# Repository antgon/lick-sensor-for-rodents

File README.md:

# Lick sensor for rodents

A device for measuring licking behaviour in rodents in real time.

This project describes a lick sensor developed for the purpose of
measuring licking behaviour in laboratory animals. Licking behaviour,
and in particular the analysis of lick microstructure, is a useful tool
for studying ingestive behaviour, motivation, and food preference.

2021-2025 Antonio González

## Features

The lick sensor is built with a Raspberry Pi Pico microcontroller board
and a capacitive touch sensor. It can can be used with standard water
bottles for rodents, and does not require modifications to animal home
cages. The lick sensor can thus be adapted to a wide range of
experimental setups.

Licks are detected in real time with millisecond precision from one or
many drink bottles simultaneously. The data can be recorded using any
standard data acquisition system; it can be sent to a computer for
storage; and/or it can be used for real-time control of additional
laboratory hardware such as LEDs for optogenetics.

### Variants

Different variants of the lick sensor are possible, depending on the
number of drink bottles required, and also on whether lick data is to be
recorded "raw" (i.e. as a continuous vector of on/off, digital data
samples), or saved in the form of lick events (timestamps).

Details of each of these options can be found in the relevant
directories. Briefly,

* [**One bottle, one BNC output**](bottle-x1-bnc-out). This is the
  simplest lick sensor variant: it uses only one drink bottle. Licks
  from this bottle are detected and directed to a BNC connector from
  where they can be recorded with a data acquisition system and/or used
  for driving additional laboratory hardware in real time.

* [**Several bottles, BNC outputs**](bottle-x6-bnc-out). Similar to the
  setup above but using more than one drink bottle.

* [**Many bottles (up to 12), USB output**](bottle-x12-usb-out). Here,
  lick events (timestamps) from many drink bottles are detected and sent
  to a computer connected to the microcontroller with a USB cable. The
  construction of this lick sensor is very simple and a data-acquisition
  system is not required. On the other hand, the software side of it is
  more elaborate: it is necessary to install and run Python software in
  the host computer.

* [**Many bottles (up to 24), USB output**](bottle-x24-usb-out). As
  above, but using 2 touch-detection boards to handle up to 24 drink
  bottles simultaneously.

## Requirements

### Lick sensor hardware

* Drinking bottle(s). Any standard drinking bottle for rodents should
  work. We use the Crystal Deluxe Mini Bottle 75 ml ([Classic Pet
  Products, UK, cat. num.
  0190](https://classicpetproducts.co.uk/product/crystal-deluxe-mini-bottle-75ml/))
  obtained from a local pet shop.
* [Raspberry Pi
  Pico](https://www.raspberrypi.com/products/raspberry-pi-pico)
  microcontroller board.
* Capacitive touch sensor module. We use [Adafruit product ID
  1982](https://www.adafruit.com/product/1982); up to 12 water bottles
  can be connected to one of these modules[^1]. Other manufacturers sell
  touch sensors based on the MPR121 and any of these should work equally
  well.
* Stranded-core cable (e.g. 24 AWG or 26 AWG standard hook-up cable).
* A USB cable for the Raspberry Pi Pico.
* BNC connector(s). Optional, depending on the sensor variant chosen.

Some means to put the components together, for example:

* Perforated board or stripboard.
* Jumper wires.
* Soldering tools.

Supplier information and ordering codes are listed in
[material.md](docs/material.md).

### Lick sensor software

* C development tools and the knowledge/ability to build a project for
  the Raspberry Pi Pico, as described in the [Pico
  documentation](https://datasheets.raspberrypi.com/pico/getting-started-with-pico.pdf).
* MPR121 library for the Raspberry Pi Pico, available at
  https://github.com/antgon/pico-mpr121.

### Data acquisition hardware

Depending on the variant chosen, you will need either:

* A standard laboratory data-acquisition system. This is only needed
  if you want to record *raw* data (e.g.
  [bottle-x1-bnc-out](bottle-x1-bnc-out)), or
* A computer to record lick events. We use a Raspberry Pi 4 computer
  with very good results. See [bottles-x12-usb-out](bottles-x12-usb-out)
  for details.

[^1]: Adafruit sell two different MPR121 touch sensor breakouts under
    the same Product ID 1982: the original, header-only version, and the
    STEMMA QT version. Both work in the same way, and the PCBs are the
    same size (and look similar). Be aware, however, that **the pins are
    in a different order**.

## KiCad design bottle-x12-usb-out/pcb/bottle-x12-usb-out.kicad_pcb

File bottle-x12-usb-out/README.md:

# Lick sensor: up to 12 bottles, detect lick events

This variant of the sensor detects licks from up to 12 drink bottles
simultaneously. Lick events (timestamps) are sent to a host computer
connected to the Raspberry Pi Pico via a USB cable.

## Wiring and operation

Wiring of the components is simple and a stripboard can be used to
facilitate this; see folder [pcb](pcb).

For logging the data, a host computer connected to the lick sensor must
read and save the data received. We use for that a Raspberry Pi 4 (or 5)
computer:

* Compile `lick_events_usb.c` and flash into the Pico.
* Save the provided Python script (`lick_events_reader.py`) to the host
  computer.
* Connect the drink bottles to the lick sensor.
* Connect the Pico to the host computer.
* Boot the host computer. Open a terminal and run the Python script
  above. Lick data will be logged to a local text file. To stop, press
  Ctrl+C.
* To convert the data in the text file to a more readable form suitable
  for analysis, run the Python script
  [`events-to-long.py`](../utils/events-to-long.py).

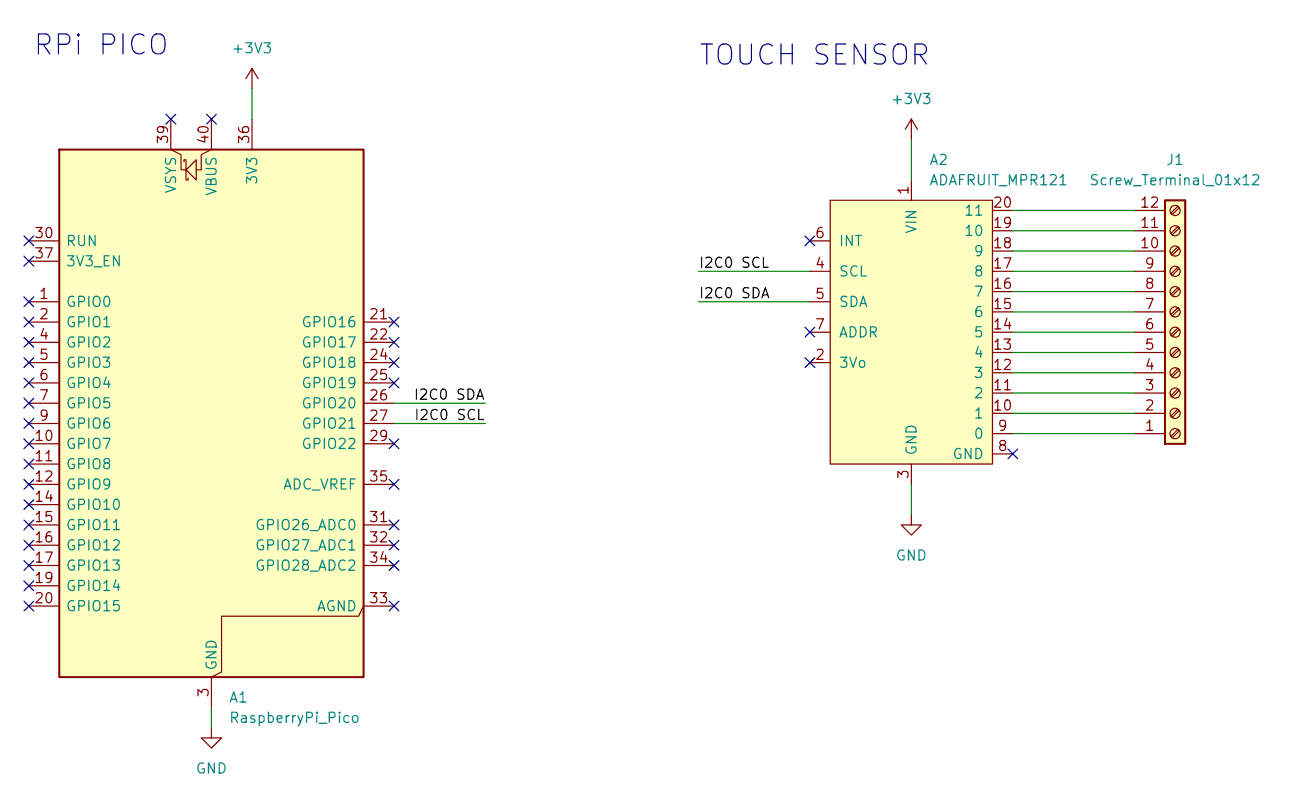
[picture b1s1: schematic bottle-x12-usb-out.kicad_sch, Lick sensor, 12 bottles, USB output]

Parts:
A1: RaspberryPi_Pico; RaspberryPi_Pico_Common_THT
A2: ADAFRUIT_MPR121
J1: Screw_Terminal_01x12; TerminalBlock_Phoenix_MPT-0,5-12-2.54_1x12_P2.54mm_Horizont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

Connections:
+3V3: A1.36 (3V3), A2.1 (VIN)
/I2C0 SCL: A1.27 (GPIO21), A2.4 (SCL)
/I2C0 SDA: A1.26 (GPIO20), A2.5 (SDA)
GND: A1.3 (GND), A1.8 (GND), A1.13 (GND), A1.18 (GND), A1.23 (GND), A1.28 (GND), A1.38 (GND), A2.3 (GND)
unnamed: A2.9 (0), J1.1
unnamed: A2.10 (1), J1.2
unnamed: A2.11 (2), J1.3
unnamed: A2.12 (3), J1.4
unnamed: A2.13 (4), J1.5
unnamed: A2.14 (5), J1.6
unnamed: A2.15 (6), J1.7
unnamed: A2.16 (7), J1.8
unnamed: A2.17 (8), J1.9
unnamed: A2.18 (9), J1.10
unnamed: A2.19 (10), J1.11
unnamed: A2.20 (11), J1.12

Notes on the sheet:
TOUCH SENSOR
RPi PICO

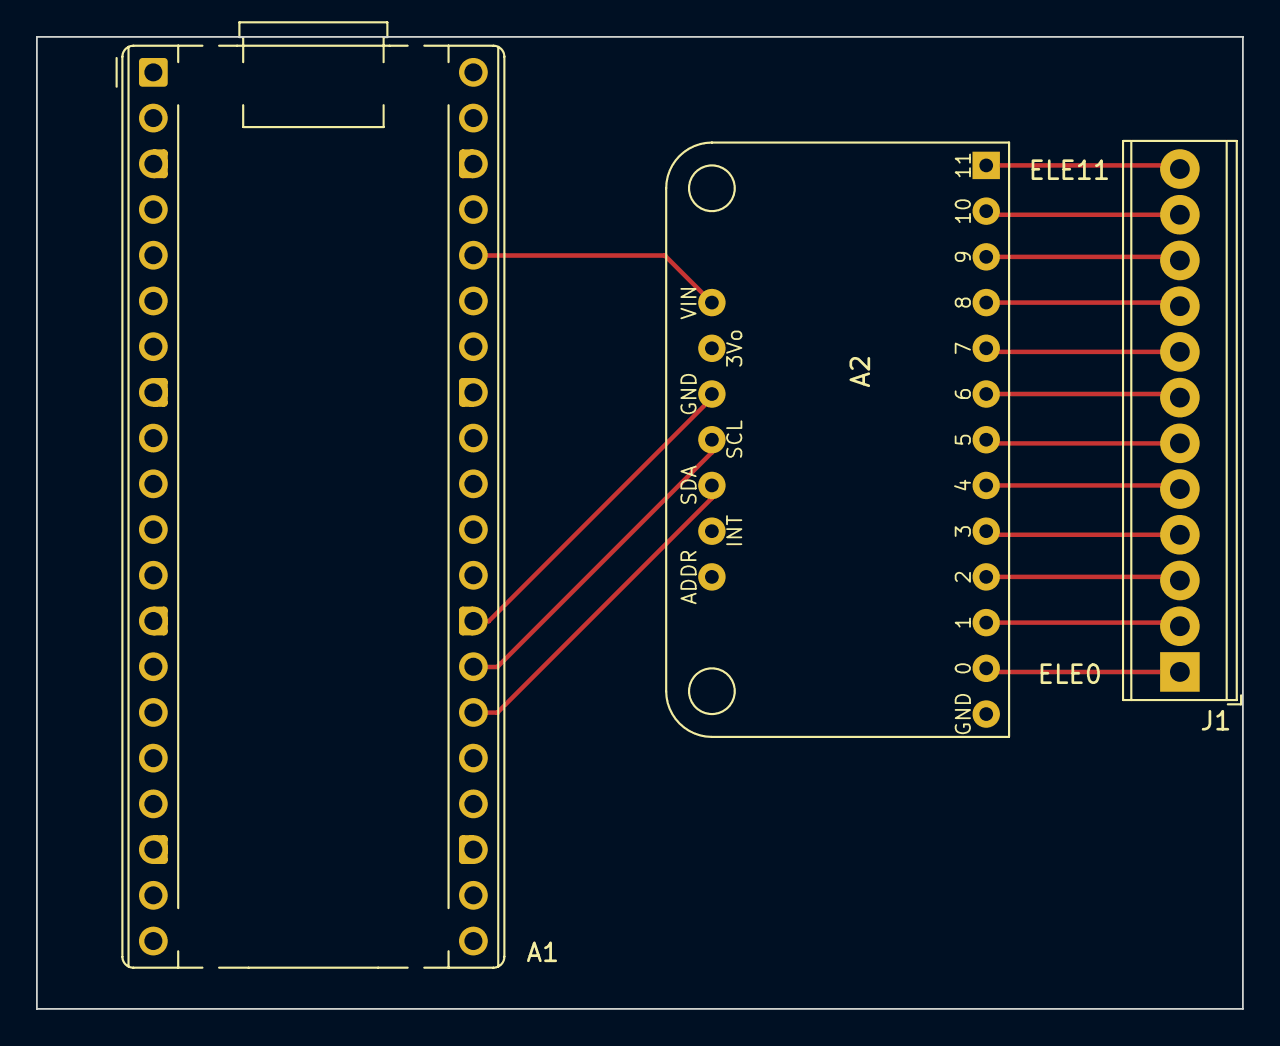
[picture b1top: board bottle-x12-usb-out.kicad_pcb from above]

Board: 2 copper layers, 67.0 x 54.0 mm, 3 parts (0 on the bottom side), 16 nets.

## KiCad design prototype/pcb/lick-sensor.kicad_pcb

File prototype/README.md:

# Lick sensor prototype

This prototype was designed for testing the lick sensor while observing
the effects of changing the sensor's settings: an LCD and four push
buttons allow to change the settings of the MPR121 capacitive sensor on
the fly. This helps tune the sensor and evaluate its ability to detect
licks under varying circumstances.

There are two BNC connectors: one outputs the digital signal, i.e. 0s
and 1s, with 1s indicating licks. The other outputs the analog signal
from the capacitive sensor, which helps visualise the changes in
capacitance that occur with licking. With these two outputs connected to
a data acquisition board, the behaviour of the touch sensor can be
assessed.

## Building and operation

1. This prototype is designed to be built on a perforated board. Details
   can be found in the [pcb](pcb) folder.

2. Program the microcontroller: compile `app/main.c` and flash into the
   Raspberry Pi Pico. See the [Pico
   documentation](https://www.raspberrypi.com/documentation/microcontrollers/pico-series.html#documentation)
   for details of how to do this. Note that in addition to standard Pico
   libraries, these 3 libraries are required:
    * [lcd16x2_i2c.h](https://github.com/antgon/pico-lcd16x2_i2c)
    * [mcp48x1.h](https://github.com/antgon/pico-mcp48x1)
    * [mpr121.h](https://github.com/antgon/pico-mpr121)

3. Connect a drink bottle to the board. Connect the two BNC outputs to a
   data acquisition (DAQ) board. Power up the Raspberry Pi Pico. The
   lick sensor will output data to the BNCs every 20 ms (50 Hz).

4. Modify the MCP121 settings using the buttons (see [docs](docs)
   for detailed instructions), use the DAQ to observe the effects of
   doing this.

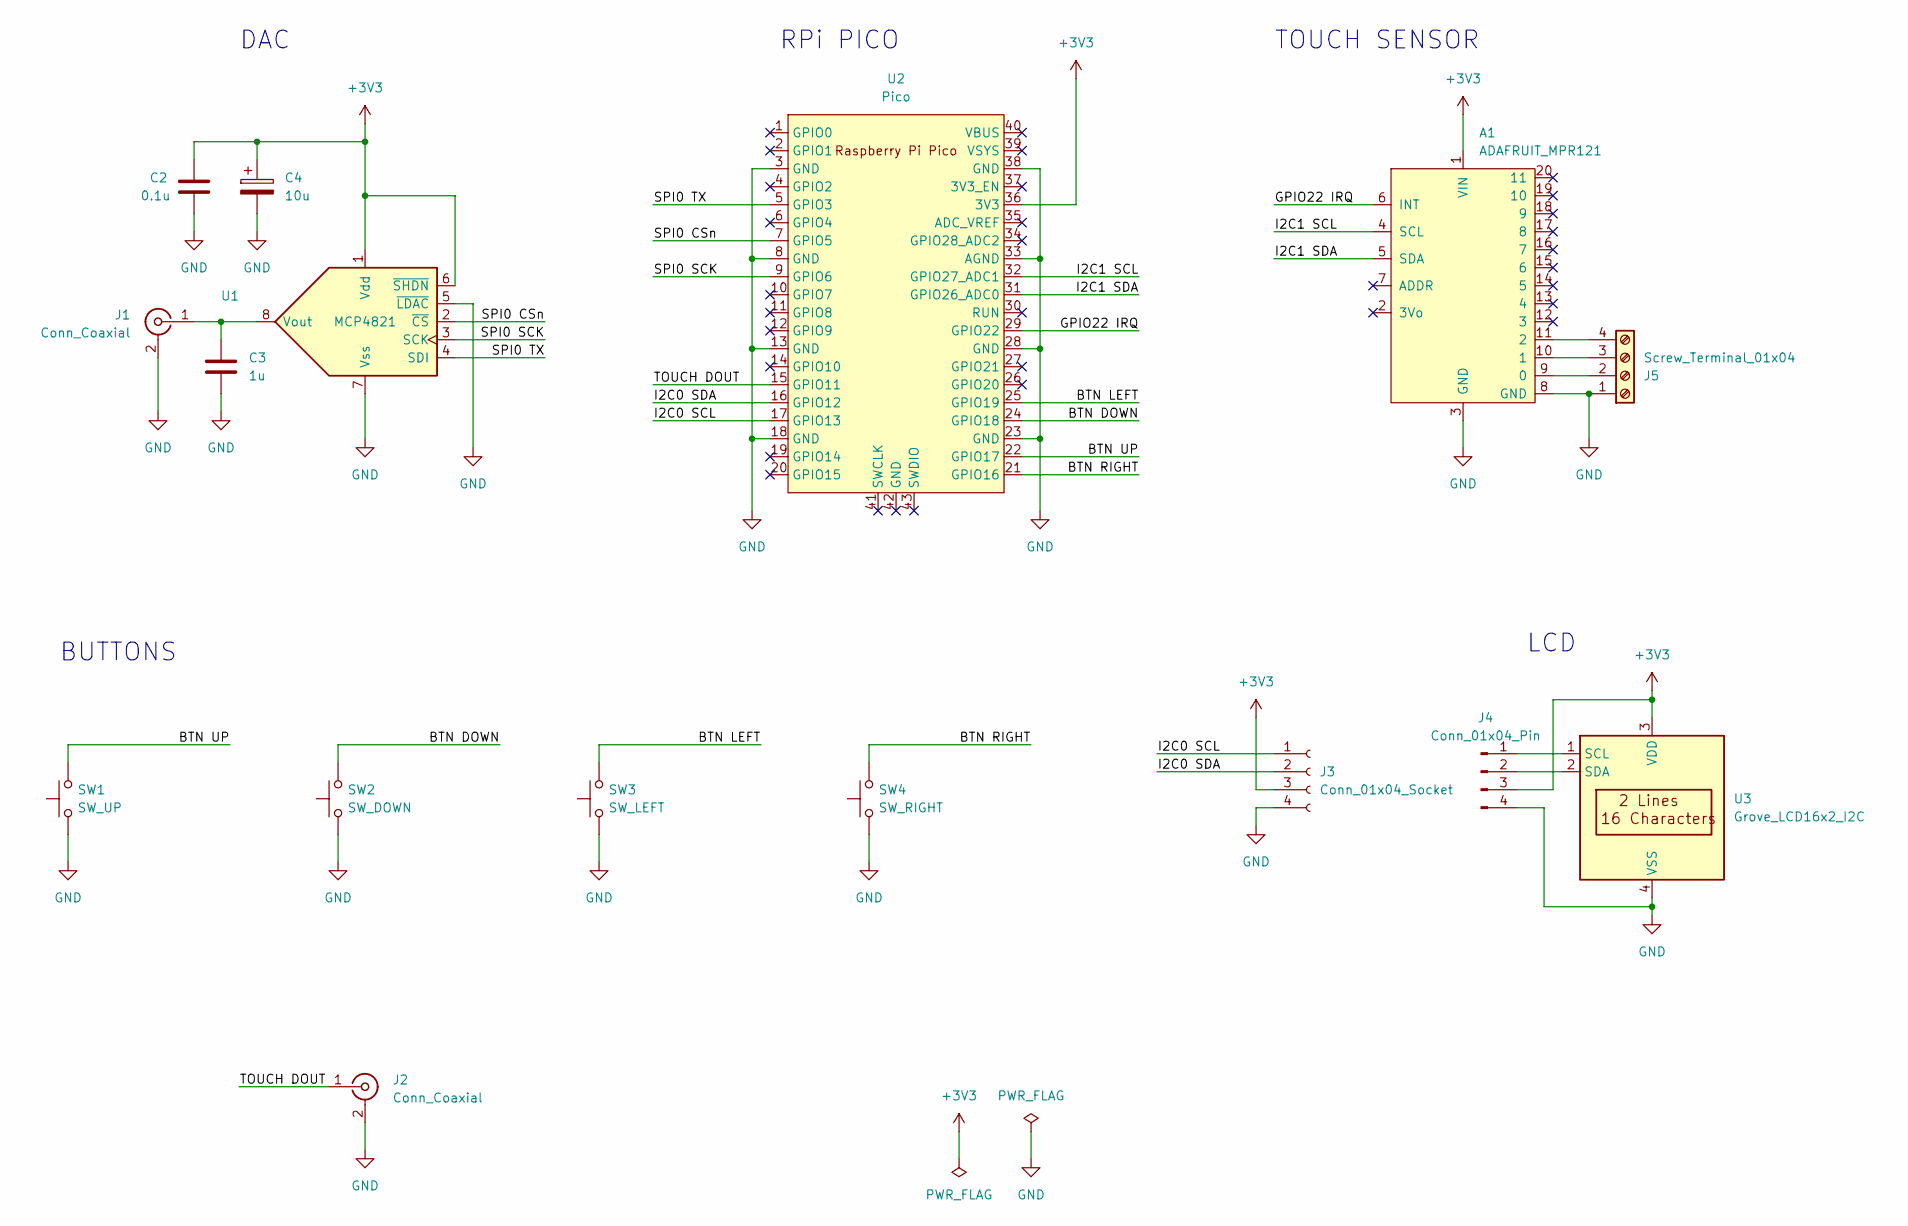
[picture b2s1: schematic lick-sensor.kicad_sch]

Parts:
A1: ADAFRUIT_MPR121
C2: 0.1u; C_Disc_D5.0mm_W2.5mm_P2.50mm
C3: 1u; C_Disc_D5.0mm_W2.5mm_P2.50mm
C4: 10u; CP_Radial_Tantal_D5.0mm_P2.50mm
J1, J2: Conn_Coaxial; BNC_Amphenol_B6252HB-NPP3G-50_Horizontal
J3: Conn_01x04_Socket; Molex_Nano-Fit_105313-xx04_1x04_P2.50mm_Horizontal
J4: Conn_01x04_Pin; Molex_Nano-Fit_105313-xx04_1x04_P2.50mm_Horizontal
J5: Screw_Terminal_01x04; TerminalBlock_Phoenix_MPT-0,5-4-2.54_1x04_P2.54mm_Horizontal
SW1: SW_UP; SW_PUSH_6mm
SW2: SW_DOWN; SW_PUSH_6mm
SW3: SW_LEFT; SW_PUSH_6mm
SW4: SW_RIGHT; SW_PUSH_6mm
U1: MCP4821; DIP-8_W7.62mm
U2: Pico; RPi_Pico_SMD_TH
U3: Grove_LCD16x2_I2C

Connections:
+3V3: A1.1 (VIN), C2.1, C4.1, J3.3, J4.3, U1.1 (Vdd), U1.6 (~SHDN), U2.36 (3V3), U3.3 (VDD)
/BTN DOWN: SW2.2, U2.24 (GPIO18)
/BTN LEFT: SW3.2, U2.25 (GPIO19)
/BTN RIGHT: SW4.2, U2.21 (GPIO16)
/BTN UP: SW1.2, U2.22 (GPIO17)
/GPIO22 IRQ: A1.6 (INT), U2.29 (GPIO22)
/I2C0 SCL: J3.1, U2.17 (GPIO13)
/I2C0 SDA: J3.2, U2.16 (GPIO12)
/I2C1 SCL: A1.4 (SCL), U2.32 (GPIO27_ADC1)
/I2C1 SDA: A1.5 (SDA), U2.31 (GPIO26_ADC0)
/SPI0 CSn: U1.2 (~CS), U2.7 (GPIO5)
/SPI0 SCK: U1.3 (SCK), U2.9 (GPIO6)
/SPI0 TX: U1.4 (SDI), U2.5 (GPIO3)
/TOUCH DOUT: J2.1 (In), U2.15 (GPIO11)
GND: A1.3 (GND), A1.8 (GND), C2.2, C3.2, C4.2, J1.2 (Ext), J2.2 (Ext), J3.4, J4.4, J5.1, SW1.1, SW2.1, SW3.1, SW4.1, U1.5 (~LDAC), U1.7 (Vss), U2.3 (GND), U2.8 (GND), U2.13 (GND), U2.18 (GND), U2.23 (GND), U2.28 (GND), U2.33 (AGND), U2.38 (GND), U3.4 (VSS)
unnamed: A1.9 (0), J5.2
unnamed: A1.10 (1), J5.3
unnamed: A1.11 (2), J5.4
unnamed: C3.1, J1.1 (In), U1.8 (Vout)
unnamed: J4.1, U3.1 (SCL)
unnamed: J4.2, U3.2 (SDA)

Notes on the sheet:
BUTTONS
TOUCH SENSOR
LCD
DAC
RPi PICO

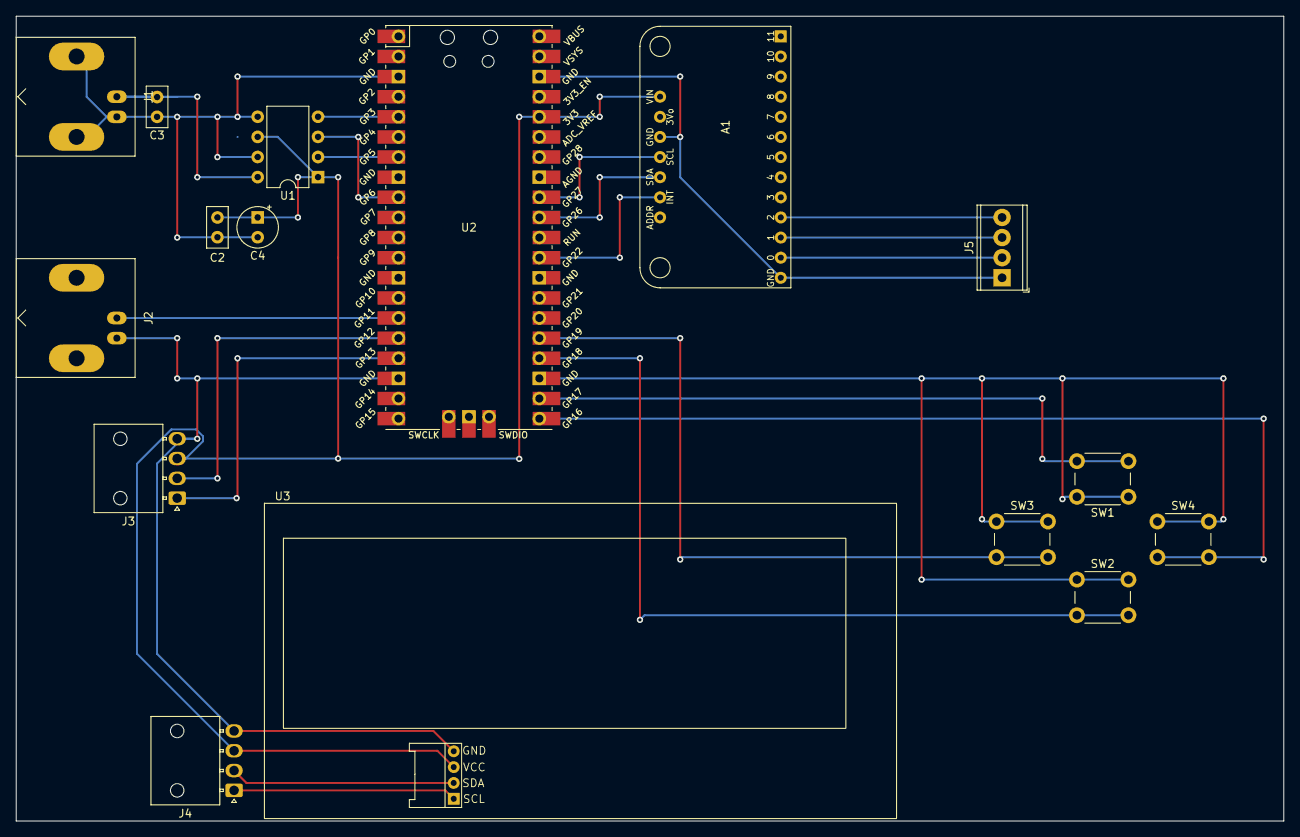
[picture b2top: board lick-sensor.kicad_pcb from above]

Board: 2 copper layers, 160.0 x 101.6 mm, 16 parts (0 on the bottom side), 21 nets.

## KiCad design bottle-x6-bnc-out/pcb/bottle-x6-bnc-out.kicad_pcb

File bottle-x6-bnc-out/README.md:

# Lick sensor: several bottles, BNC outputs

Lick sensor for more than one drinking bottle, with continuous raw
output stream.

## Description

This is an extension of the lick sensor used for only one bottle
([bottle-x1-bnc-out](../bottle-x1-bnc-out)), and programming and
operation is thus similar as described there.

Wiring details are in the folder [pcb](pcb).

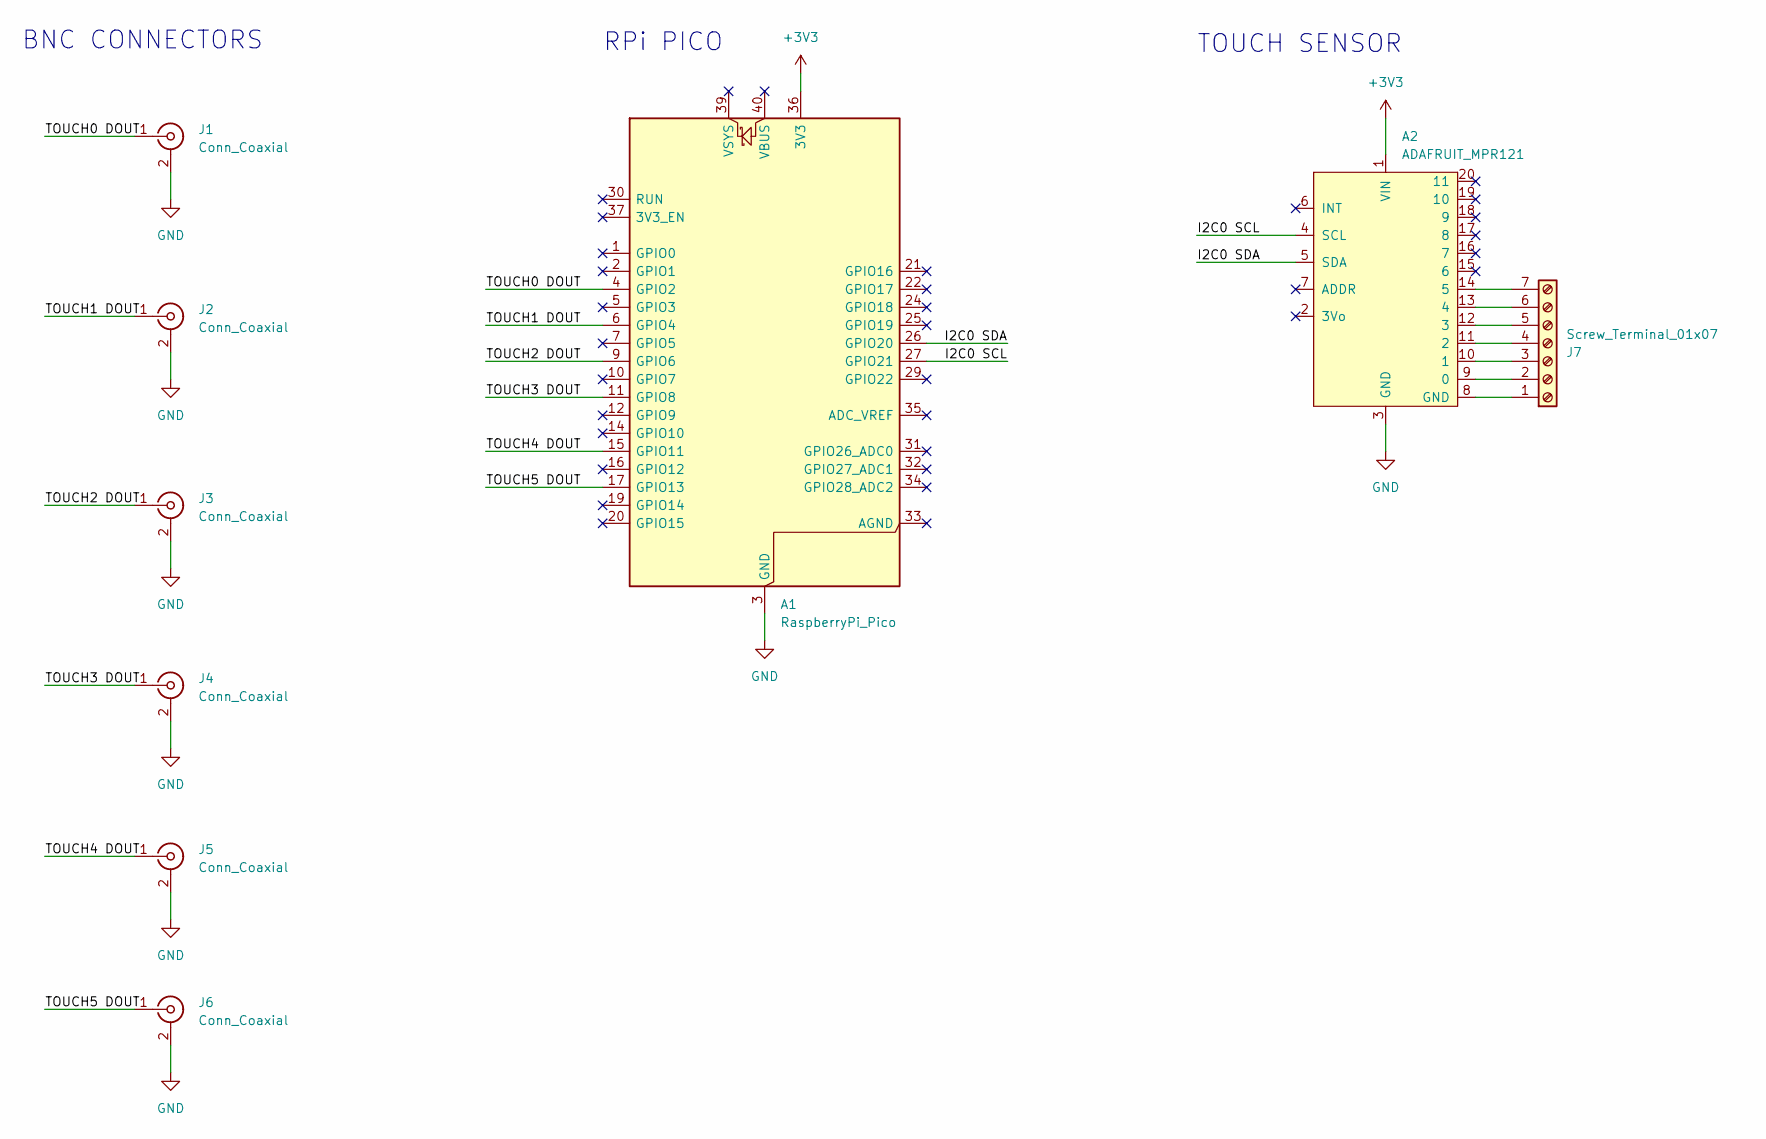
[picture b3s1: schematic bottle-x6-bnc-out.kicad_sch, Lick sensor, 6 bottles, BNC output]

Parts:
A1: RaspberryPi_Pico; RaspberryPi_Pico_Common_THT
A2: ADAFRUIT_MPR121
J1, J2, J3, J4, J5, J6: Conn_Coaxial; BNC_Amphenol_B6252HB-NPP3G-50_Horizontal
J7: Screw_Terminal_01x07; TerminalBlock_Phoenix_MPT-0,5-7-2.54_1x07_P2.54mm_Horizontal

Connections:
+3V3: A1.36 (3V3), A2.1 (VIN)
/I2C0 SCL: A1.27 (GPIO21), A2.4 (SCL)
/I2C0 SDA: A1.26 (GPIO20), A2.5 (SDA)
/TOUCH0 DOUT: A1.4 (GPIO2), J1.1 (In)
/TOUCH1 DOUT: A1.6 (GPIO4), J2.1 (In)
/TOUCH2 DOUT: A1.9 (GPIO6), J3.1 (In)
/TOUCH3 DOUT: A1.11 (GPIO8), J4.1 (In)
/TOUCH4 DOUT: A1.15 (GPIO11), J5.1 (In)
/TOUCH5 DOUT: A1.17 (GPIO13), J6.1 (In)
GND: A1.3 (GND), A1.8 (GND), A1.13 (GND), A1.18 (GND), A1.23 (GND), A1.28 (GND), A1.38 (GND), A2.3 (GND), J1.2 (Ext), J2.2 (Ext), J3.2 (Ext), J4.2 (Ext), J5.2 (Ext), J6.2 (Ext)
unnamed: A2.9 (0), J7.2
unnamed: A2.10 (1), J7.3
unnamed: A2.11 (2), J7.4
unnamed: A2.12 (3), J7.5
unnamed: A2.13 (4), J7.6
unnamed: A2.14 (5), J7.7
unnamed: A2.8 (GND), J7.1

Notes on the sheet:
BNC CONNECTORS
TOUCH SENSOR
RPi PICO

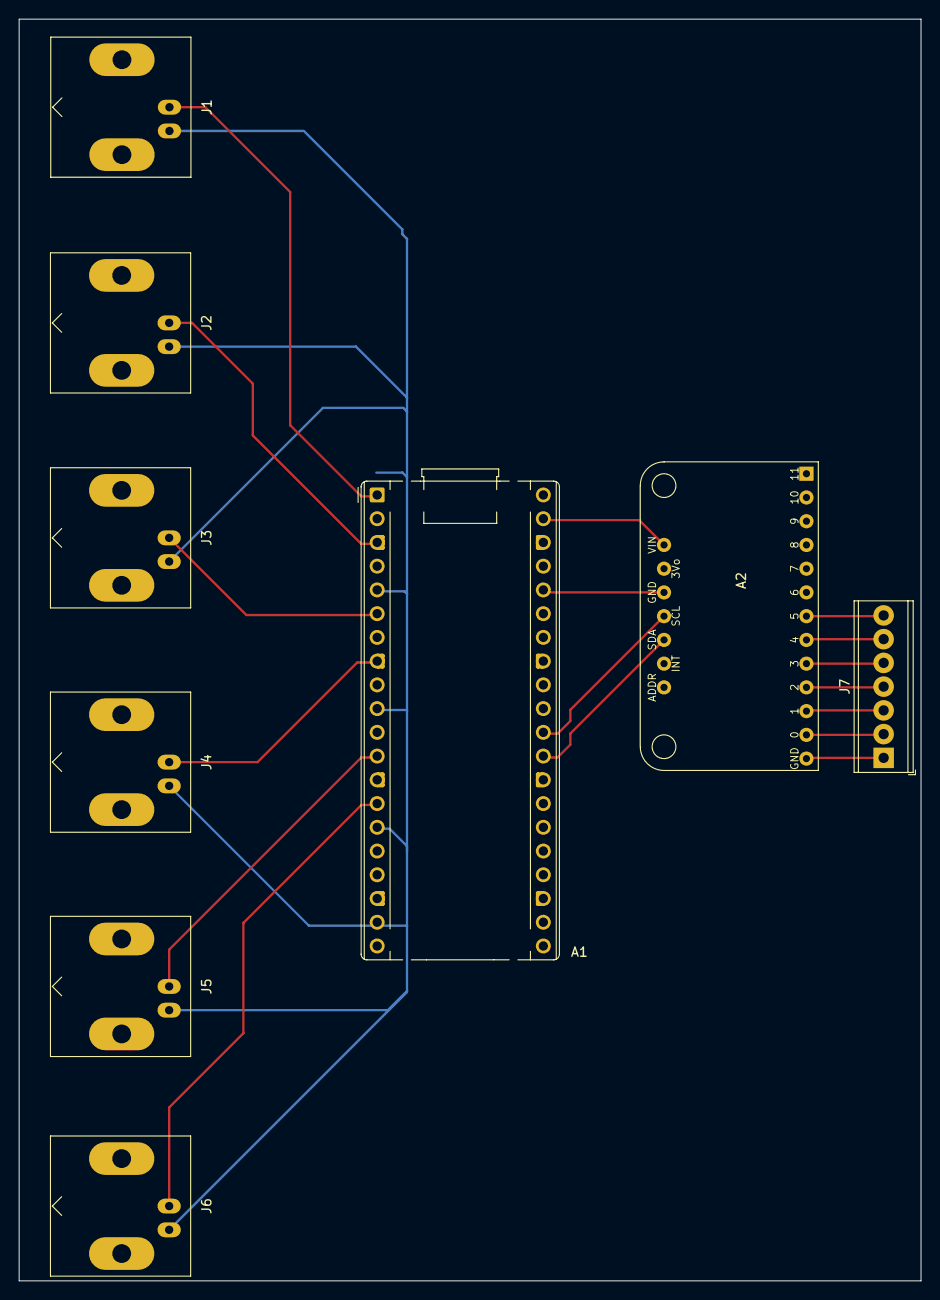
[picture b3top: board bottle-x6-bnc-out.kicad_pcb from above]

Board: 2 copper layers, 96.5 x 135.0 mm, 9 parts (0 on the bottom side), 17 nets.

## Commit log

2026-01-06 Fixed typo
2026-01-06 Fixed typos
2026-01-07 Updated banners
